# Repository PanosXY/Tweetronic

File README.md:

# Tweetronic
A system that takes the twitter posts and translates them into commands for a wireless 4-channel relay board.<br />
The firmware has not implemented yet.

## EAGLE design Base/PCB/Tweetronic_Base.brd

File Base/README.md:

# Tweetronic-Base
This is the twitter-posts parser

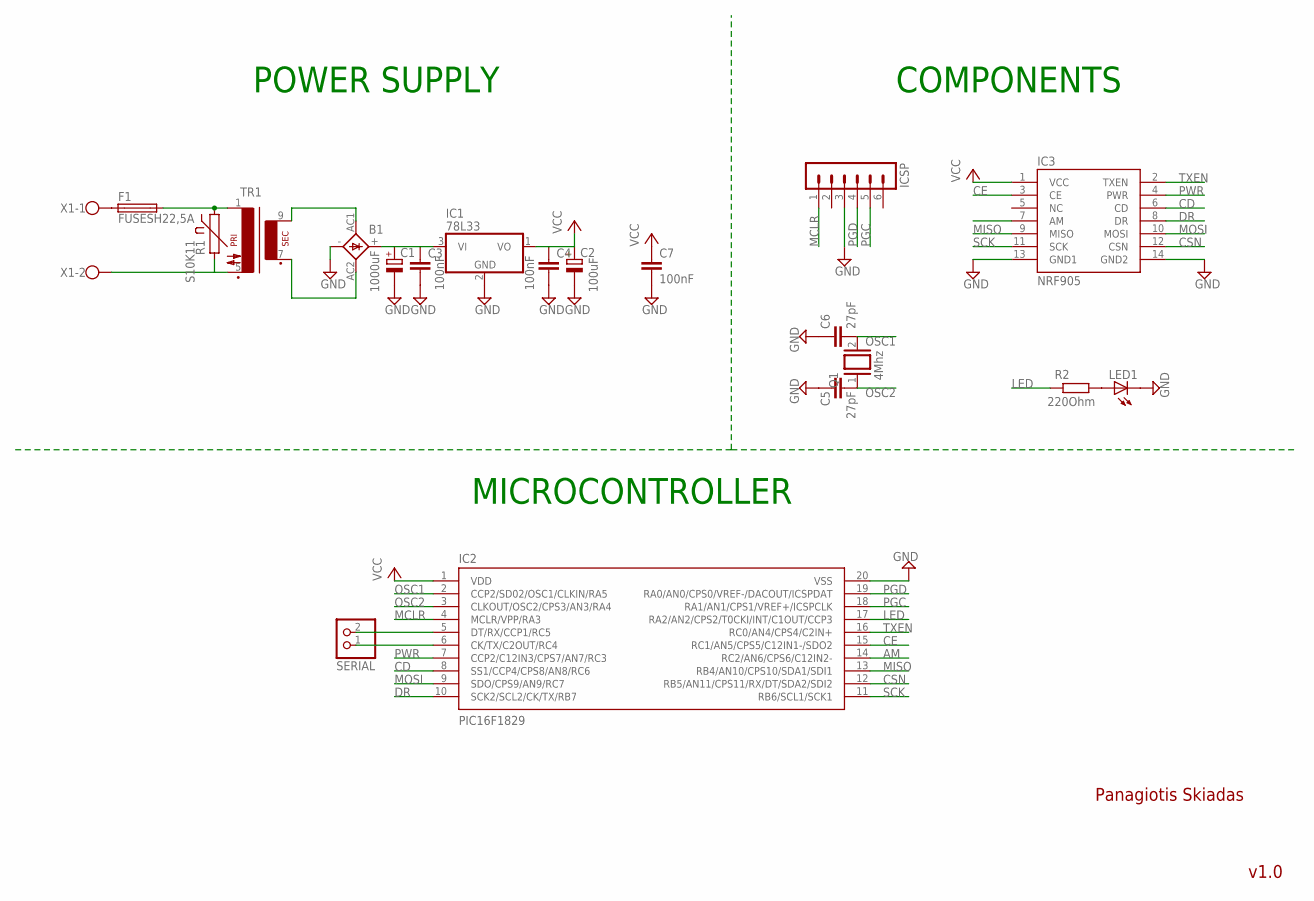
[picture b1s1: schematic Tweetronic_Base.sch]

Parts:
B1: 1KAB
C1: 1000uF; E5-13
C2: 100uF; E3,5-8
C3, C4, C7: 100nF; C5B3
C5, C6: 27pF; C2.5-3
F1: FUSESH22,5A; SH22,5A
IC1: 78L33; TO92
IC2: PIC16F1829; DIL20
IC3: NRF905; 2X07
ICSP: MA06-1
LED1: LED5MM
Q1: 4Mhz; QS
R1: S10K11
R2: 220Ohm; 0207/10
SERIAL: PINHD-1X2; 1X02
TR1: VR11
X1: W237-102

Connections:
AM: IC2.14 (RC2/AN6/CPS6/C12IN2-), IC3.7 (AM)
CD: IC2.8 (SS1/CCP4/CPS8/AN8/RC6), IC3.6 (CD)
CE: IC2.15 (RC1/AN5/CPS5/C12IN1-/SDO2), IC3.3 (CE)
CSN: IC2.12 (RB5/AN11/CPS11/RX/DT/SDA2/SDI2), IC3.12 (CSN)
DR: IC2.10 (SCK2/SCL2/CK/TX/RB7), IC3.8 (DR)
GND: B1.-, C1.-, C2.-, C3.2, C4.2, C5.1, C6.1, C7.2, IC1.2 (GND), IC2.20 (VSS), IC3.13 (GND1), IC3.14 (GND2), ICSP.3, LED1.K (C)
LED: IC2.17 (RA2/AN2/CPS2/T0CKI/INT/C1OUT/CCP3), R2.2
MCLR: IC2.4 (MCLR/VPP/RA3), ICSP.1
MISO: IC2.13 (RB4/AN10/CPS10/SDA1/SDI1), IC3.9 (MISO)
MOSI: IC2.9 (SDO/CPS9/AN9/RC7), IC3.10 (MOSI)
unnamed: F1.1, X1.1
unnamed: F1.2, R1.1, TR1.1
unnamed: R1.2, TR1.5 (P2), X1.2
unnamed: B1.AC1, TR1.9 (S4)
unnamed: B1.AC2, TR1.7 (S3)
unnamed: B1.+, C1.+, C3.1, IC1.3 (VI)
unnamed: IC2.5 (DT/RX/CCP1/RC5), SERIAL.2
unnamed: IC2.6 (CK/TX/C2OUT/RC4), SERIAL.1
unnamed: LED1.A, R2.1
OSC1: C6.2, IC2.2 (CCP2/SD02/OSC1/CLKIN/RA5), Q1.2
OSC2: C5.2, IC2.3 (CLKOUT/OSC2/CPS3/AN3/RA4), Q1.1
PGC: IC2.18 (RA1/AN1/CPS1/VREF+/ICSPCLK), ICSP.5
PGD: IC2.19 (RA0/AN0/CPS0/VREF-/DACOUT/ICSPDAT), ICSP.4
PWR: IC2.7 (CCP2/C12IN3/CPS7/AN7/RC3), IC3.4 (PWR)
SCK: IC2.11 (RB6/SCL1/SCK1), IC3.11 (SCK)
TXEN: IC2.16 (RC0/AN4/CPS4/C2IN+), IC3.2 (TXEN)
VCC: C2.+, C4.1, C7.1, IC1.1 (VO), IC2.1 (VDD), IC3.1 (VCC)

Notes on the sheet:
POWER SUPPLY
COMPONENTS
MICROCONTROLLER
Panagiotis Skiadas
v1.0

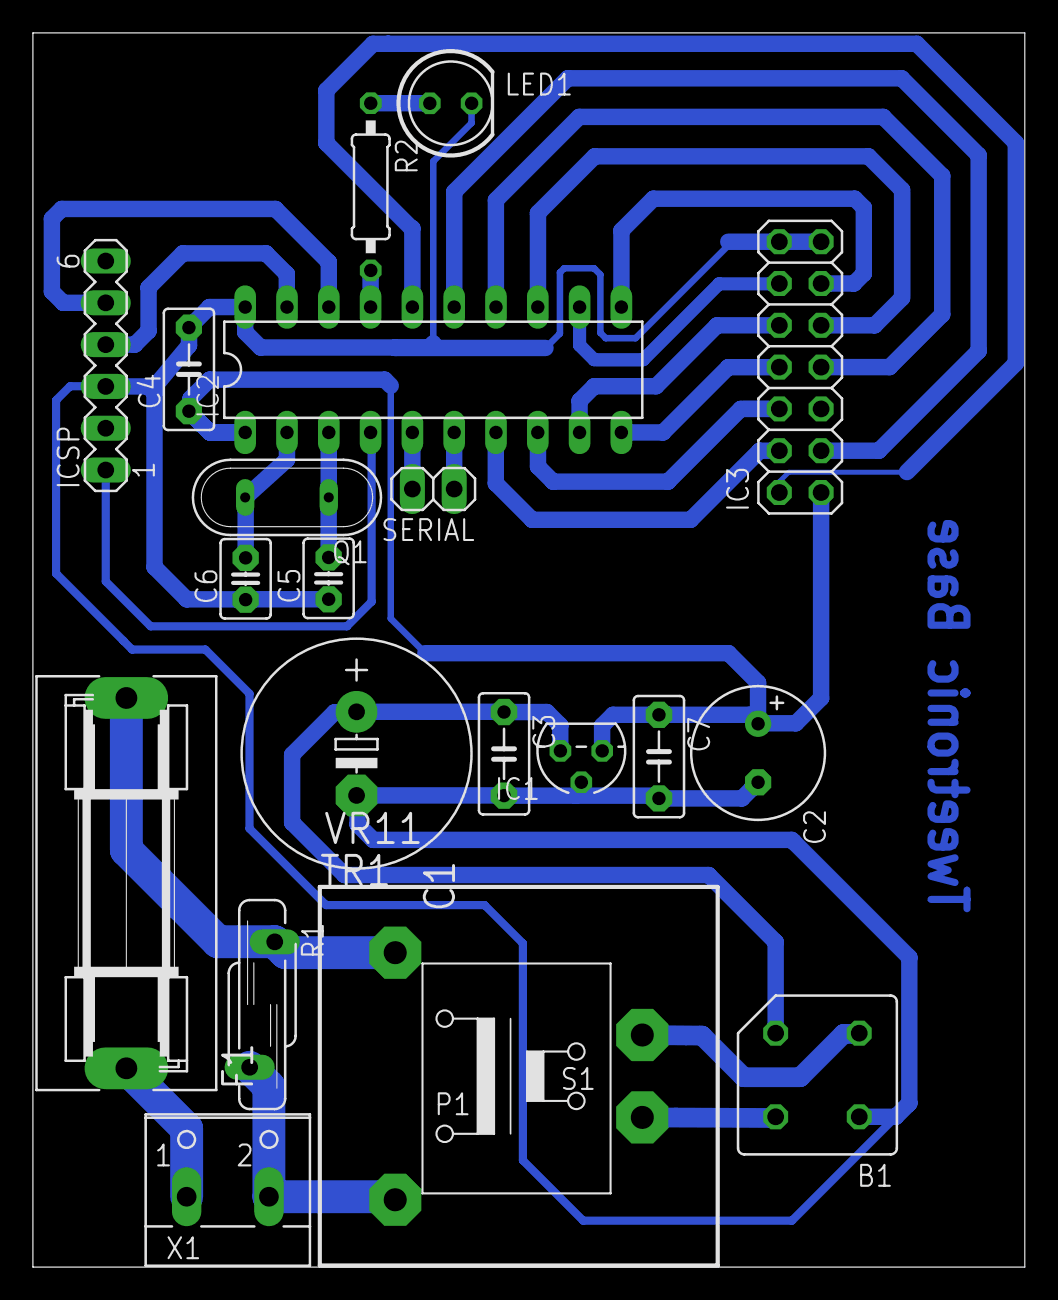
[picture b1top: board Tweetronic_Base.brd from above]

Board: 2 copper layers, 60.3 x 75.0 mm, 20 parts (0 on the bottom side), 27 nets.

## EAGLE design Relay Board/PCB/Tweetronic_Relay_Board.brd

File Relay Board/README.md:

# Tweetronic-Relay-Board
This is the 4-channel Relay Board

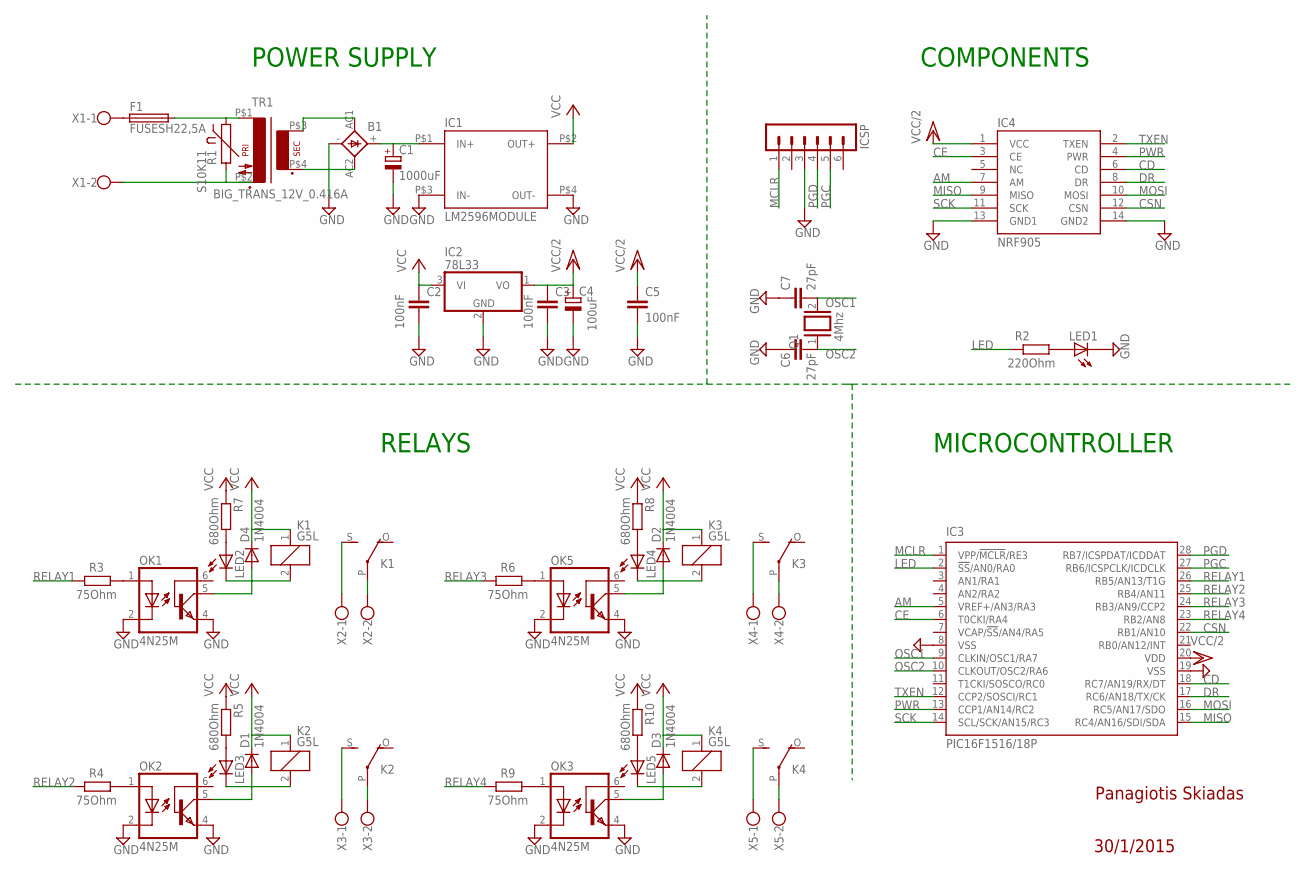
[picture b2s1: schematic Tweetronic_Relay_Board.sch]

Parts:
B1: 1KAB
C1: 1000uF; E5-13
C2, C3, C5: 100nF; C5B3
C4: 100uF; E3,5-8
C6, C7: 27pF; C2.5-3
D1, D2, D3, D4: 1N4004; DO41-10
F1: FUSESH22,5A; SH22,5A
IC1: LM2596MODULE; MODULE
IC2: 78L33; TO92
IC3: PIC16F1516/18P; DIL28-3
IC4: NRF905; 2X07
ICSP: MA06-1
K1, K2, K3, K4: G5L; G5LE
LED1: LED5MM
LED2, LED3, LED4, LED5: LED3MM
OK1, OK2, OK3, OK5: 4N25M; DIL06
Q1: 4Mhz; QS
R1: S10K11
R2: 220Ohm; 0207/10
R3, R4, R6, R9: 75Ohm; 0207/10
R5, R7, R8, R10: 680Ohm; 0207/10
TR1: BIG_TRANS_12V_0.416A; BIG_TRANSF_12V_0.416A
X1, X2, X3, X4, X5: W237-102

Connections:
AM: IC3.5 (VREF+/AN3/RA3), IC4.7 (AM)
CD: IC3.18 (RC7/AN19/RX/DT), IC4.6 (CD)
CE: IC3.6 (T0CKI/RA4), IC4.3 (CE)
CSN: IC3.22 (RB1/AN10), IC4.12 (CSN)
DR: IC3.17 (RC6/AN18/TX/CK), IC4.8 (DR)
GND: B1.-, C1.-, C2.2, C3.2, C4.-, C5.2, C6.1, C7.1, IC1.P$3 (IN-), IC1.P$4 (OUT-), IC2.2 (GND), IC3.8 (VSS), IC3.19 (VSS), IC4.13 (GND1), IC4.14 (GND2), ICSP.3, LED1.K (C), OK1.2 (C), OK1.4 (EMI), OK2.2 (C), OK2.4 (EMI), OK3.2 (C), OK3.4 (EMI), OK5.2 (C), OK5.4 (EMI)
LED: IC3.2 (!SS!/AN0/RA0), R2.2
MCLR: IC3.1 (VPP/!MCLR!/RE3), ICSP.1
MISO: IC3.15 (RC4/AN16/SDI/SDA), IC4.9 (MISO)
MOSI: IC3.16 (RC5/AN17/SDO), IC4.10 (MOSI)
unnamed: F1.1, X1.1
unnamed: F1.2, R1.1, TR1.P$1 (P1)
unnamed: R1.2, TR1.P$2 (P2), X1.2
unnamed: B1.AC2, TR1.P$4 (S3)
unnamed: B1.AC1, TR1.P$3 (S4)
unnamed: B1.+, C1.+, IC1.P$1 (IN+)
unnamed: OK5.1 (A), R6.1
unnamed: LED1.A, R2.1
unnamed: OK1.1 (A), R3.1
unnamed: OK2.1 (A), R4.1
unnamed: D1.A, K2.2, LED3.K (C), OK2.5 (COL)
unnamed: LED3.A, R5.2
unnamed: K2.S, X3.1
unnamed: K2.P, X3.2
unnamed: D4.A, K1.2, LED2.K (C), OK1.5 (COL)
unnamed: OK3.1 (A), R9.1
unnamed: LED2.A, R7.2
unnamed: K1.S, X2.1
unnamed: K1.P, X2.2
unnamed: D2.A, K3.2, LED4.K (C), OK5.5 (COL)
unnamed: LED4.A, R8.2
unnamed: K3.S, X4.1
unnamed: K3.P, X4.2
unnamed: D3.A, K4.2, LED5.K (C), OK3.5 (COL)
unnamed: LED5.A, R10.2
unnamed: K4.S, X5.1
unnamed: K4.P, X5.2
OSC1: C7.2, IC3.9 (CLKIN/OSC1/RA7), Q1.2
OSC2: C6.2, IC3.10 (CLKOUT/OSC2/RA6), Q1.1
PGC: IC3.27 (RB6/ICSPCLK/ICDCLK), ICSP.5
PGD: IC3.28 (RB7/ICSPDAT/ICDDAT), ICSP.4
PWR: IC3.13 (CCP1/AN14/RC2), IC4.4 (PWR)
RELAY1: IC3.26 (RB5/AN13/T1G), R3.2
RELAY2: IC3.25 (RB4/AN11), R4.2
RELAY3: IC3.24 (RB3/AN9/CCP2), R6.2
RELAY4: IC3.23 (RB2/AN8), R9.2
SCK: IC3.14 (SCL/SCK/AN15/RC3), IC4.11 (SCK)
TXEN: IC3.12 (CCP2/SOSCI/RC1), IC4.2 (TXEN)
VCC: C2.1, D1.C, D2.C, D3.C, D4.C, IC1.P$2 (OUT+), IC2.3 (VI), K1.1, K2.1, K3.1, K4.1, R5.1, R7.1, R8.1, R10.1
VCC/2: C3.1, C4.+, C5.1, IC2.1 (VO), IC3.20 (VDD), IC4.1 (VCC)

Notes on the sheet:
POWER SUPPLY
COMPONENTS
RELAYS
MICROCONTROLLER
Panagiotis Skiadas
30/1/2015

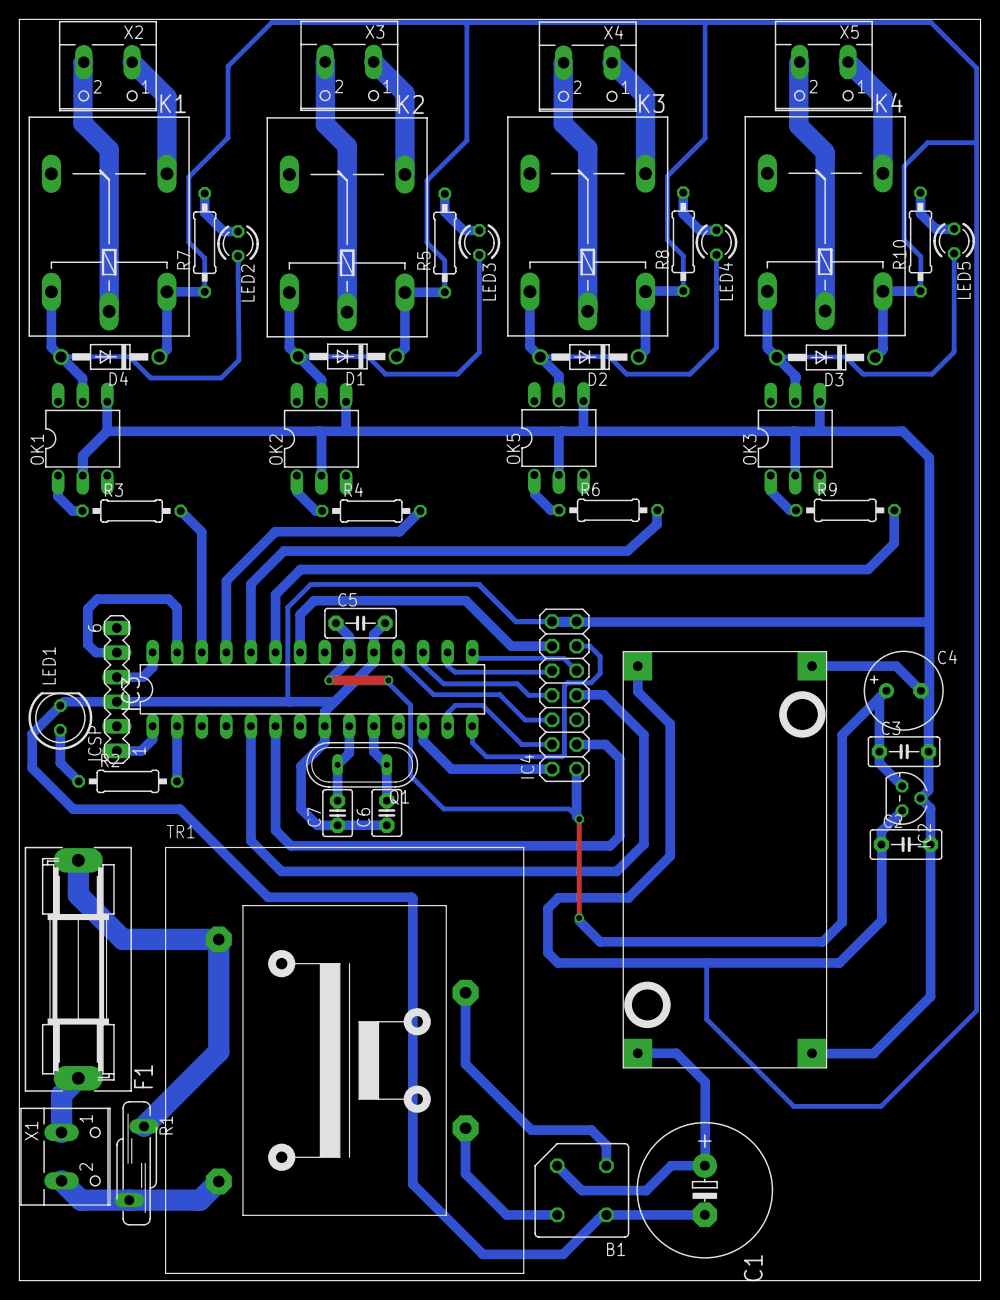
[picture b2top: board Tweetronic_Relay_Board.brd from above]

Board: 2 copper layers, 99.3 x 130.3 mm, 48 parts (0 on the bottom side), 50 nets.
